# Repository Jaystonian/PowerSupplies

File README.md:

# PowerSupplies
Various power supplies or supply-related devices

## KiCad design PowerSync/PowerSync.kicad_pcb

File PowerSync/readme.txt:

Project: Commodore C128D Power Domain Synchronizer
Creator: Jaystonian
Date:    2020-09-28
Purpose: My C128D power supply was updated with modern switching regulation,
  which rarely caused a black startup screen due to 9vac and 5vdc powering on
  at different times.  In my case, the 12vdc activates >1.0 seconds after 9vac
  and the 5vdc doesn't come on until after the 12vdc.  
  
  This device triggers a power-on pulse to the dual-coil latching relays when 
  5VDC is finally active.  During power-off, a charge is stored in capacitor 
  C1 to provide about 120mJ of energy to the reset coils.  It only requires 
  about 45mJ for a 5VDC 300mA 30ms pulse, and can draw extra capacitance from 
  the 5v power domain of other system boards it is attached to.

  *PCB should be 2oz copper clad or heavier

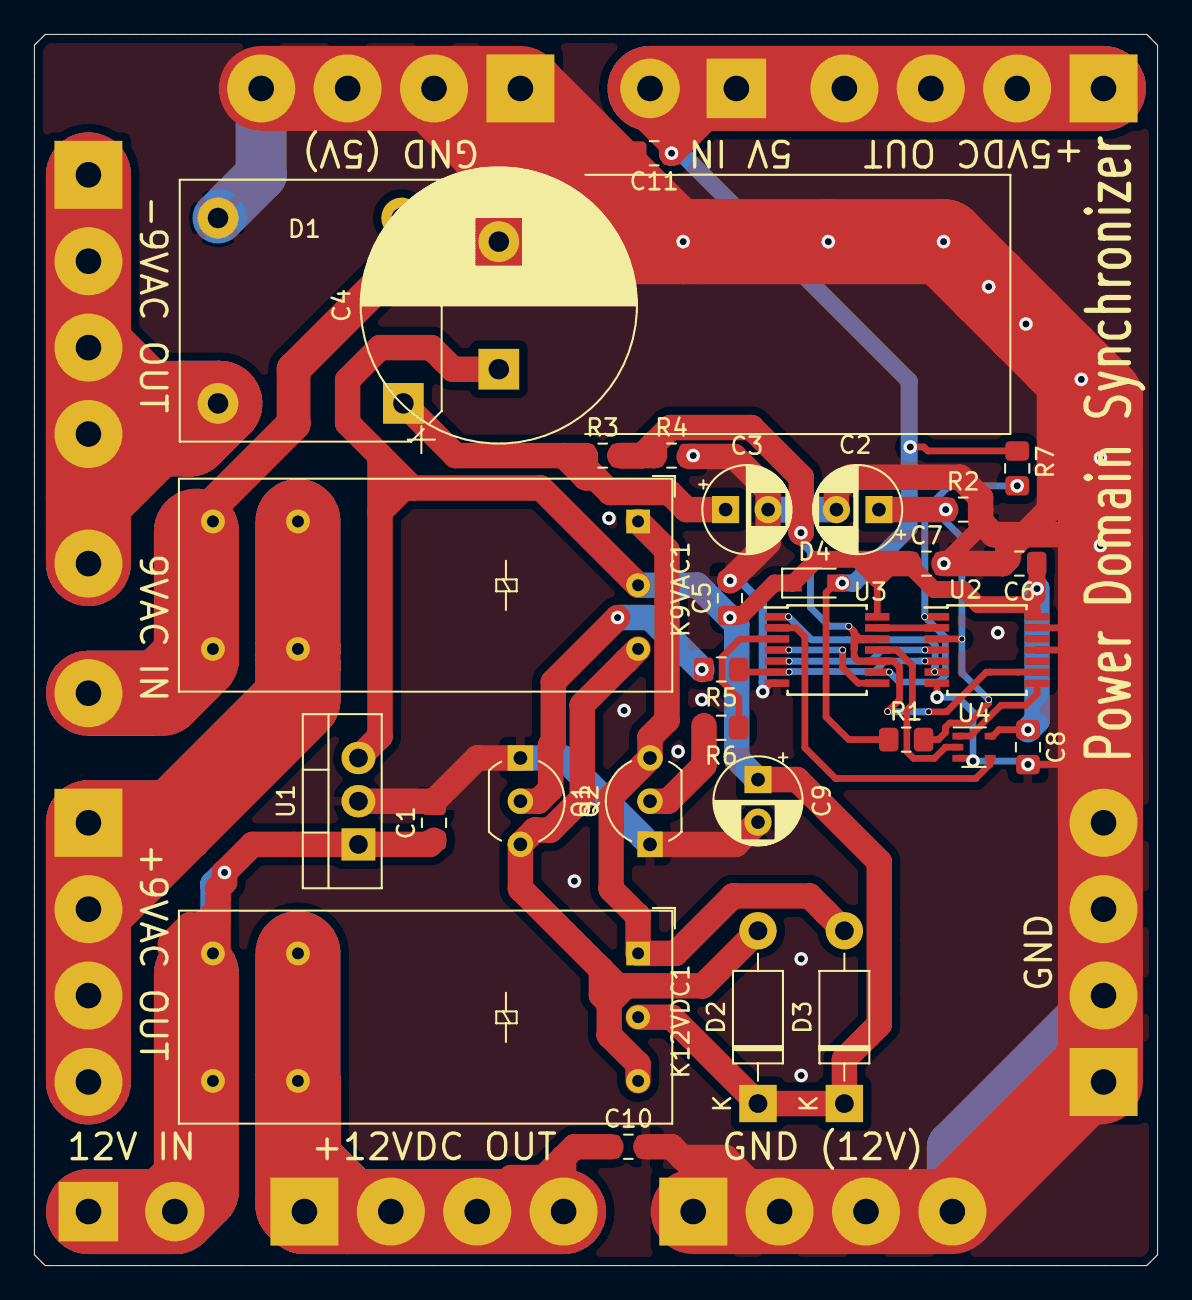
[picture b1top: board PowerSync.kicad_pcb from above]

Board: 2 copper layers, 66.0 x 72.4 mm, 41 parts (0 on the bottom side), 25 nets.

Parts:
5V IN: +5VDC; SolderWirePad_1x02_P5.08mm_Drill1.5mm
9VAC: -9VAC; SolderWirePad_1x01_Drill1.5mm
12V IN: +12VDC; SolderWirePad_1x02_P5.08mm_Drill1.5mm
+5VDC OUT, +9VAC OUT, +12VDC OUT: SolderWirePad_1x04_P5.08mm_Drill1.5mm
-9VAC OUT: SolderWirePad_1x04_P5.08mm_Drill1.5mm
C1, C5: 220n; C_0805_2012Metric_Pad1.15x1.40mm_HandSolder
C2, C3: 1u; CP_Radial_D5.0mm_P2.50mm
C4: 10000u; CP_Radial_D16.0mm_P7.50mm
C6, C10, C11: 100n; C_0805_2012Metric_Pad1.15x1.40mm_HandSolder
C7: 47n; C_0805_2012Metric_Pad1.15x1.40mm_HandSolder
C8: 10n; C_0805_2012Metric_Pad1.15x1.40mm_HandSolder
C9: 10u; CP_Radial_D5.0mm_P2.50mm
D1: D_Bridge_+A-A; Diode_Bridge_15.1x15.1x6.3mm_P10.9mm
D2, D3: 1N4001; D_DO-41_SOD81_P10.16mm_Horizontal
D4: NSR0530HT1G; D_SOD-323_HandSoldering
GND: SolderWirePad_1x04_P5.08mm_Drill1.5mm
GND (5V): GND; SolderWirePad_1x04_P5.08mm_Drill1.5mm
GND (12V): SolderWirePad_1x04_P5.08mm_Drill1.5mm
IN: +9VAC; SolderWirePad_1x01_Drill1.5mm
K9VAC1, K12VDC1: G5RL-K1A-E; Relay_SPST_Omron_G5RL-K1A-E
Q1, Q2: 2N3904; TO-92_Inline_Wide
R1: 27k; R_0805_2012Metric_Pad1.15x1.40mm_HandSolder
R2: 33k; R_0805_2012Metric_Pad1.15x1.40mm_HandSolder
R3: 22k; R_0805_2012Metric_Pad1.15x1.40mm_HandSolder
R4: 10k; R_0805_2012Metric_Pad1.15x1.40mm_HandSolder
R5, R6, R7: 220; R_0805_2012Metric_Pad1.15x1.40mm_HandSolder
U1: LM7805_TO220; TO-220-3_Vertical
U2: 74HCT04; TSSOP-14_4.4x5mm_P0.65mm
U3: 74HCT08; TSSOP-14_4.4x5mm_P0.65mm
U4: 74HCT1G32; SOT-353_SC-70-5

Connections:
+5V: 5V IN.1, 5V IN.2, +5VDC OUT.1, +5VDC OUT.2, +5VDC OUT.3, +5VDC OUT.4, C11.1, D4.2, R1.1, R7.1
+9VA: D1.2, IN.1, K9VAC1.4, K9VAC1.5
+12V: 12V IN.1, 12V IN.2, C1.1, K12VDC1.4, K12VDC1.5, U1.1
/DET_5V: R7.2, U2.1, U3.9
/DET_9VAC: R3.2, R4.1, U2.9, U3.10, U3.12
/TIMER-5V: C2.1, R1.2, R2.1, U2.3
/~RELAY_RESET: D3.2, K9VAC1.1, K12VDC1.1, Q2.3
/~RELAY_SET: D2.2, K9VAC1.8, K12VDC1.8, Q1.3
GND: C1.2, C2.2, C3.2, C4.2, C5.2, C6.2, C7.2, C8.2, C9.2, C10.2, C11.2, D1.3, GND.1, GND.2, GND.3, GND.4, GND (5V).1, GND (5V).2, GND (5V).3, GND (5V).4, GND (12V).1, GND (12V).2, GND (12V).3, GND (12V).4, Q1.1, Q2.1, R2.2, R4.2, U1.2, U2.7, U2.11, U2.13, U3.7, U4.3
NEUT: 9VAC.1, -9VAC OUT.1, -9VAC OUT.2, -9VAC OUT.3, -9VAC OUT.4, D1.4
unnamed: C3.1, D1.1, R3.1
unnamed: Q1.2, R5.2
unnamed: Q2.2, R6.2
unnamed: R5.1, U2.5, U3.6
unnamed: R6.1, U3.3
unnamed: U2.2, U3.13
unnamed: U2.4, U3.5
unnamed: U2.6, U3.1
unnamed: U2.8, U4.1
unnamed: U3.2, U4.4
unnamed: U3.4, U3.8
unnamed: U3.11, U4.2
VAC: +9VAC OUT.1, +9VAC OUT.2, +9VAC OUT.3, +9VAC OUT.4, K9VAC1.3, K9VAC1.6
VCC: C4.1, C5.1, C6.1, C7.1, C8.1, C9.1, D2.1, D3.1, D4.1, K9VAC1.9, K12VDC1.9, U1.3, U2.14, U3.14, U4.5
VDD: +12VDC OUT.1, +12VDC OUT.2, +12VDC OUT.3, +12VDC OUT.4, C10.1, K12VDC1.3, K12VDC1.6
